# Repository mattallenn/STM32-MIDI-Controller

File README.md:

# STM32 MIDI Controller - STOMPR

For the full writeup, please check out my website:

https://mattallen.page/stompr.html

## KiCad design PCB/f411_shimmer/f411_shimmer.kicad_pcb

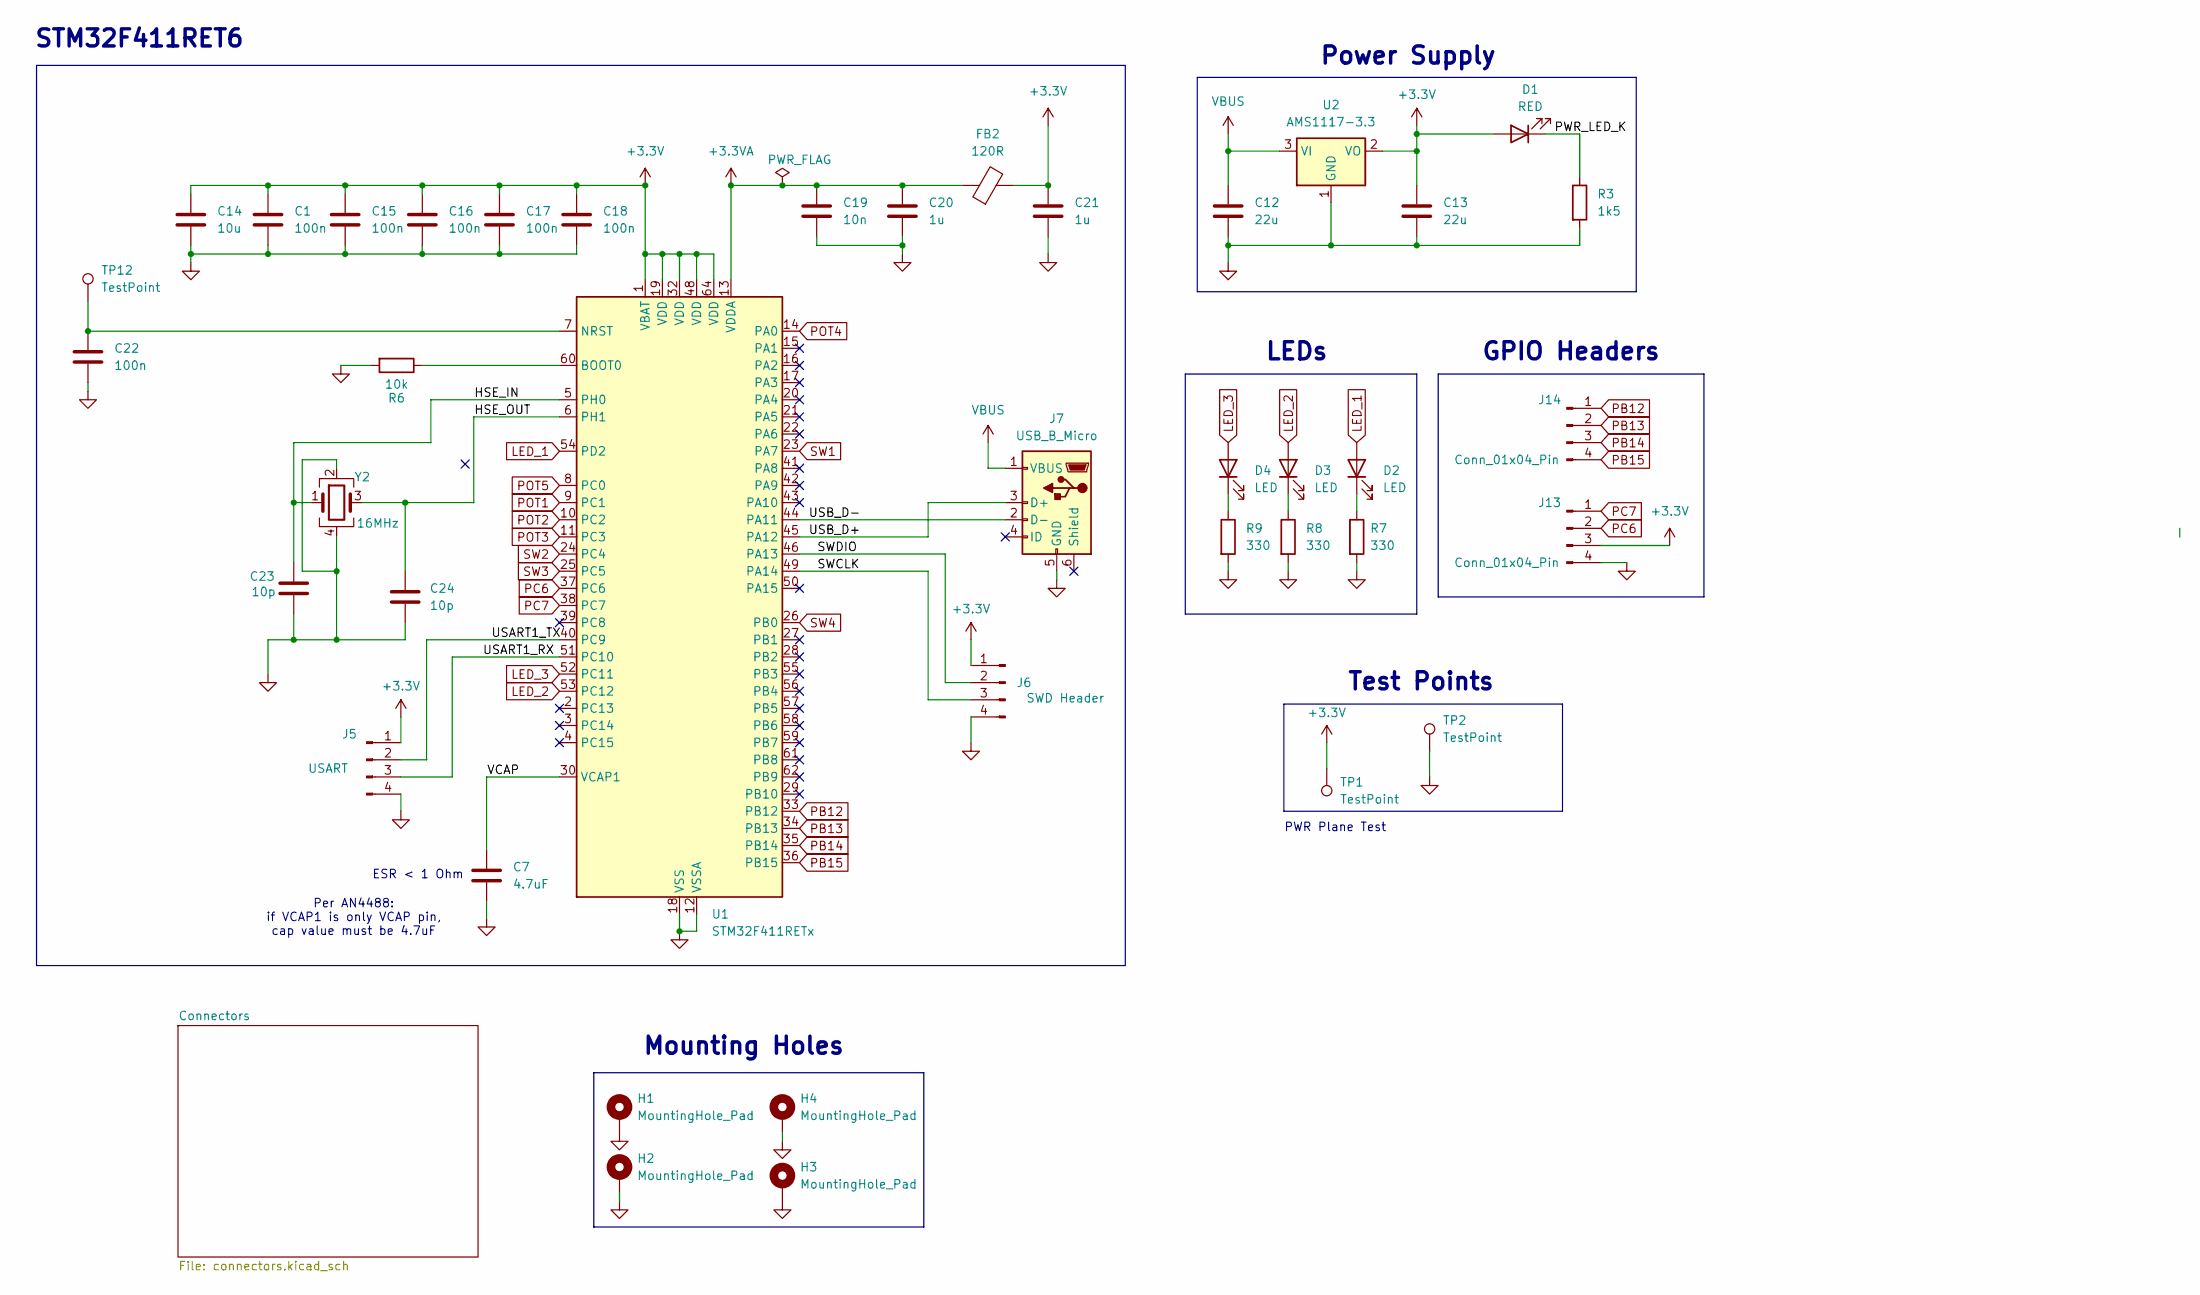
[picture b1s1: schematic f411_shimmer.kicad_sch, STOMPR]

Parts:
C1, C15, C16, C17, C18, C22: 100n; C_0603_1608Metric
C7: 4.7uF; C_0603_1608Metric
C12, C13: 22u; C_0805_2012Metric
C14: 10u; C_0603_1608Metric
C19: 10n; C_0603_1608Metric
C20, C21: 1u; C_0603_1608Metric
C23, C24: 10p; C_0603_1608Metric
D1: RED; LED_0603_1608Metric
D2, D3, D4: LED; LED_0603_1608Metric
FB2: 120R; L_0603_1608Metric
H1, H2, H3, H4: MountingHole_Pad; MountingHole_3.2mm_M3_Pad_TopBottom
J5: USART; PinHeader_1x04_P2.54mm_Vertical
J6: SWD Header; PinHeader_1x04_P2.54mm_Vertical
J7: USB_B_Micro; USB_Micro-B_Wuerth_629105150521
J13, J14: Conn_01x04_Pin; PinHeader_1x04_P2.54mm_Vertical
R3: 1k5; R_0603_1608Metric
R6: 10k; R_0603_1608Metric
R7, R8, R9: 330; R_0805_2012Metric
TP1, TP2, TP12: TestPoint; TestPoint_Pad_D1.0mm
U1: STM32F411RETx; LQFP-64_10x10mm_P0.5mm
U2: AMS1117-3.3; SOT-223-3_TabPin2
Y2: 16MHz; Crystal_SMD_3225-4Pin_3.2x2.5mm

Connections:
+3.3V: C1.1, C13.1, C14.1, C15.1, C16.1, C17.1, C18.1, C21.1, D1.2 (A), FB2.2, J5.1, J6.1, J13.3, TP1.1, U1.1 (VBAT), U1.19 (VDD), U1.32 (VDD), U1.48 (VDD), U1.64 (VDD), U2.2 (VO); also elsewhere on the board
+3.3VA: C19.1, C20.1, FB2.1, U1.13 (VDDA)
/HSE_IN: C23.1, U1.5 (PH0), Y2.1
/HSE_OUT: C24.1, U1.6 (PH1), Y2.3
/PWR_LED_K: D1.1 (K), R3.1
/SWCLK: J6.3, U1.49 (PA14)
/SWDIO: J6.2, U1.46 (PA13)
/USART1_RX: J5.3, U1.51 (PC10)
/USART1_TX: J5.2, U1.40 (PC9)
/USB_D+: J7.3 (D+), U1.45 (PA12)
/USB_D-: J7.2 (D-), U1.44 (PA11)
/VCAP: C7.1, U1.30 (VCAP1)
GND: C1.2, C7.2, C12.2, C13.2, C14.2, C15.2, C16.2, C17.2, C18.2, C19.2, C20.2, C21.2, C22.2, C23.2, C24.2, H1.1, H2.1, H3.1, H4.1, J5.4, J6.4, J7.5 (GND), J13.4, R3.2, R6.2, R7.2, R8.2, R9.2, TP2.1, U1.12 (VSSA), U1.18 (VSS), U1.31 (VSS), U1.47 (VSS), U1.63 (VSS), U2.1 (GND), Y2.2, Y2.4; also elsewhere on the board
LED_1: D2.2 (A), U1.54 (PD2)
LED_2: D3.2 (A), U1.53 (PC12)
LED_3: D4.2 (A), U1.52 (PC11)
unnamed: D2.1 (K), R7.1
unnamed: D3.1 (K), R8.1
unnamed: D4.1 (K), R9.1
unnamed: R6.1, U1.60 (BOOT0)
unnamed: C22.1, TP12.1, U1.7 (NRST)
PB12: J14.1, U1.33 (PB12)
PB13: J14.2, U1.34 (PB13)
PB14: J14.3, U1.35 (PB14)
PB15: J14.4, U1.36 (PB15)
PC6: J13.2, U1.37 (PC6)
PC7: J13.1, U1.38 (PC7)
POT1: U1.9 (PC1); also elsewhere on the board
POT2: U1.10 (PC2); also elsewhere on the board
POT3: U1.11 (PC3); also elsewhere on the board
POT4: U1.14 (PA0); also elsewhere on the board
POT5: U1.8 (PC0); also elsewhere on the board
SW1: U1.23 (PA7); also elsewhere on the board
SW2: U1.24 (PC4); also elsewhere on the board
SW3: U1.25 (PC5); also elsewhere on the board
SW4: U1.26 (PB0); also elsewhere on the board
VBUS: C12.1, J7.1 (VBUS), U2.3 (VI); also elsewhere on the board

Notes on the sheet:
LEDs
Per AN4488: if VCAP1 is only VCAP pin, cap value must be 4.7uF
Power Supply
PWR Plane Test
GPIO Headers
ESR < 1 Ohm
Mounting Holes
Test Points
STM32F411RET6

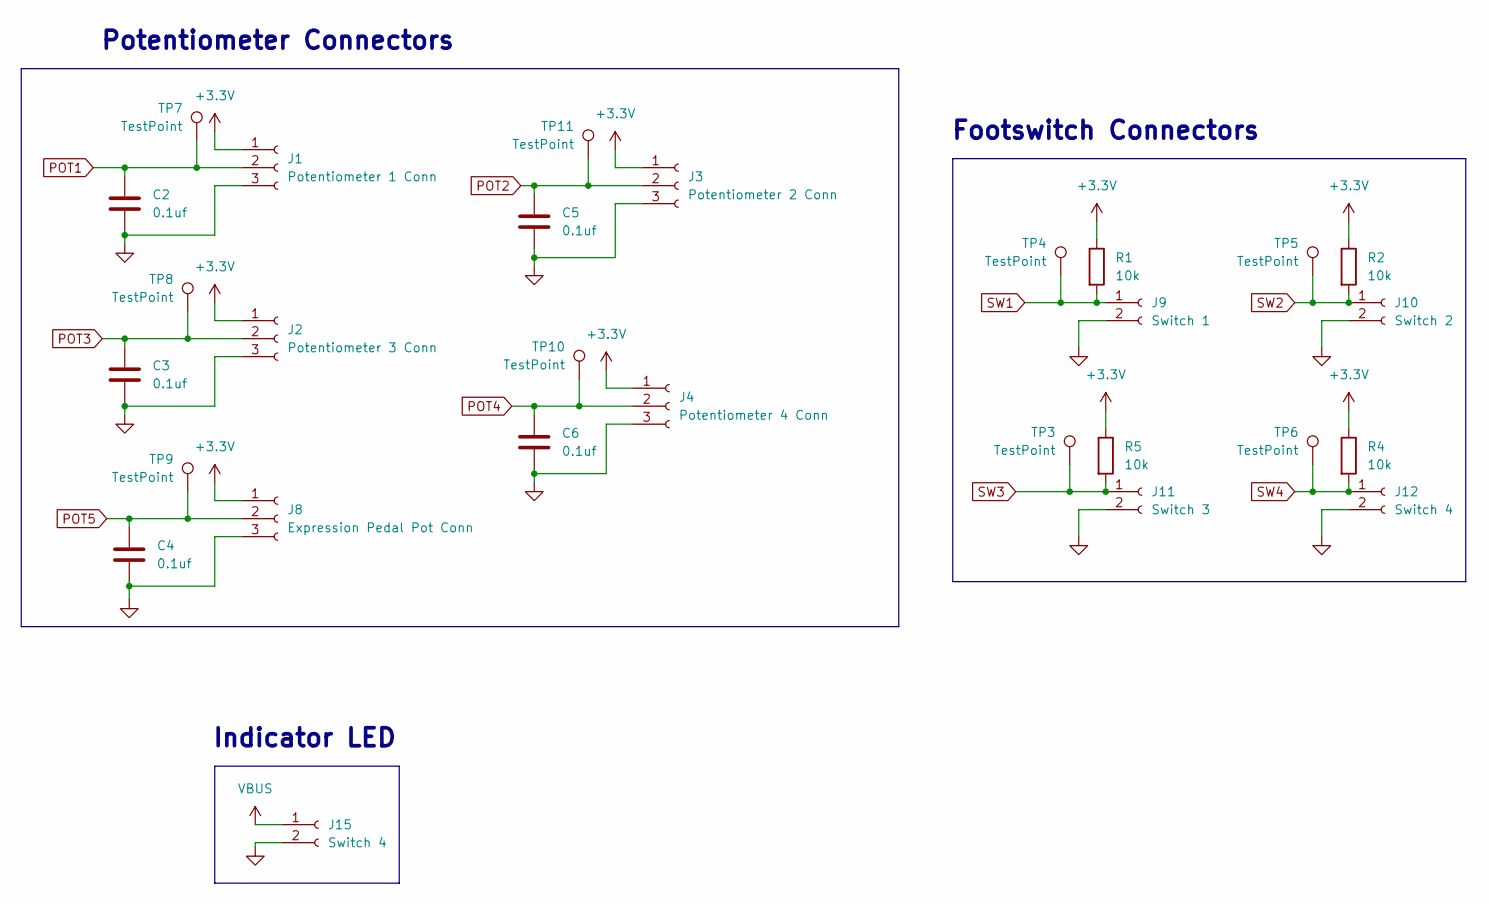
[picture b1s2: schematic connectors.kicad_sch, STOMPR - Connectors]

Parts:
C2, C3, C4, C5, C6: 0.1uf; C_0603_1608Metric
J1: Potentiometer 1 Conn; JST_EH_B3B-EH-A_1x03_P2.50mm_Vertical
J2: Potentiometer 3 Conn; JST_EH_B3B-EH-A_1x03_P2.50mm_Vertical
J3: Potentiometer 2 Conn; JST_EH_B3B-EH-A_1x03_P2.50mm_Vertical
J4: Potentiometer 4 Conn; JST_EH_B3B-EH-A_1x03_P2.50mm_Vertical
J8: Expression Pedal Pot Conn; JST_EH_B3B-EH-A_1x03_P2.50mm_Vertical
J9: Switch 1; JST_EH_B2B-EH-A_1x02_P2.50mm_Vertical
J10: Switch 2; JST_EH_B2B-EH-A_1x02_P2.50mm_Vertical
J11: Switch 3; JST_EH_B2B-EH-A_1x02_P2.50mm_Vertical
J12, J15: Switch 4; JST_EH_B2B-EH-A_1x02_P2.50mm_Vertical
R1, R2, R4, R5: 10k; R_0805_2012Metric
TP3, TP4, TP5, TP6, TP7, TP8, TP9, TP10, TP11: TestPoint; TestPoint_Pad_D1.0mm

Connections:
+3.3V: J1.1, J2.1, J3.1, J4.1, J8.1, R1.1, R2.1, R4.1, R5.1; also elsewhere on the board
GND: C2.2, C3.2, C4.2, C5.2, C6.2, J1.3, J2.3, J3.3, J4.3, J8.3, J9.2, J10.2, J11.2, J12.2, J15.2; also elsewhere on the board
POT1: C2.1, J1.2, TP7.1; also elsewhere on the board
POT2: C5.1, J3.2, TP11.1; also elsewhere on the board
POT3: C3.1, J2.2, TP8.1; also elsewhere on the board
POT4: C6.1, J4.2, TP10.1; also elsewhere on the board
POT5: C4.1, J8.2, TP9.1; also elsewhere on the board
SW1: J9.1, R1.2, TP4.1; also elsewhere on the board
SW2: J10.1, R2.2, TP5.1; also elsewhere on the board
SW3: J11.1, R5.2, TP3.1; also elsewhere on the board
SW4: J12.1, R4.2, TP6.1; also elsewhere on the board
VBUS: J15.1; also elsewhere on the board

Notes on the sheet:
Footswitch Connectors
Indicator LED
Potentiometer Connectors

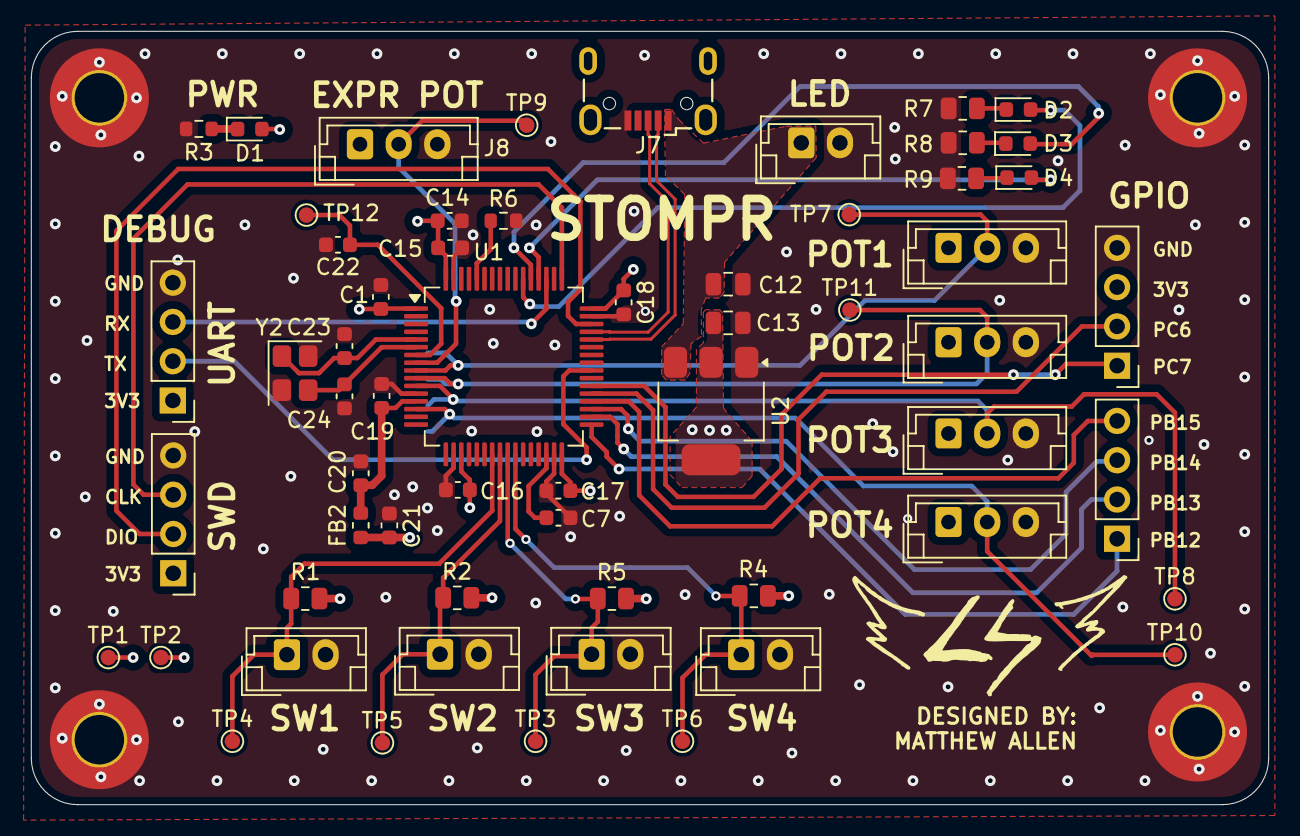
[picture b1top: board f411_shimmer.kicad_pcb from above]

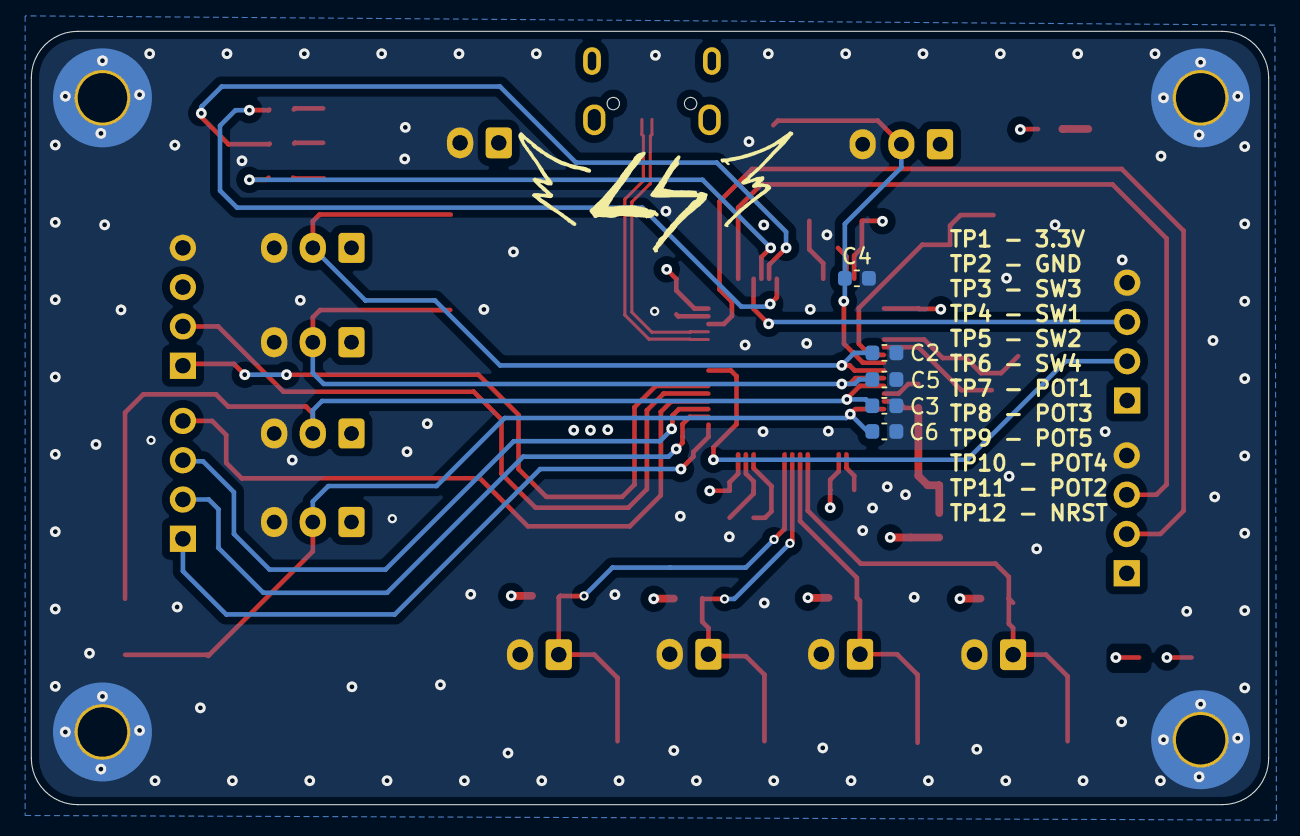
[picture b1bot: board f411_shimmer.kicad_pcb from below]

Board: 4 copper layers, 80.0 x 50.0 mm, 68 parts (5 on the bottom side), 37 nets.

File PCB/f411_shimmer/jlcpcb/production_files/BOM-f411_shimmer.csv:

Comment,Designator,Footprint,LCSC,Quantity
0.1uf,"C2,C3,C4,C5,C6",C_0603_1608Metric,C14663,5
100n,"C1,C15,C16,C17,C18,C22",C_0603_1608Metric,C14663,6
10k,"R1,R2,R4,R5",R_0805_2012Metric,C17414,4
10k,R6,R_0603_1608Metric,C25804,1
10n,C19,C_0603_1608Metric,C57112,1
10p,"C23,C24",C_0603_1608Metric,C1634,2
10u,C14,C_0603_1608Metric,C19702,1
120R,FB2,L_0603_1608Metric,C14709,1
16MHz,Y2,Crystal_SMD_3225-4Pin_3.2x2.5mm,C13738,1
1k5,R3,R_0603_1608Metric,C22843,1
1u,"C20,C21",C_0603_1608Metric,C15849,2
22u,"C12,C13",C_0805_2012Metric,C45783,2
330,"R7,R8,R9",R_0805_2012Metric,C17630,3
4.7uF,C7,C_0603_1608Metric,C19666,1
AMS1117-3.3,U2,SOT-223-3_TabPin2,C6186,1
LED,"D2,D3,D4",LED_0603_1608Metric,C2286,3
RED,D1,LED_0603_1608Metric,C2286,1
STM32F411RETx,U1,LQFP-64_10x10mm_P0.5mm,C94355,1
Switch 4,J12,JST_EH_B2B-EH-A_1x02_P2.50mm_Vertical,,1
TestPoint,TP4,TestPoint_Pad_D1.0mm,,1
Switch 3,J11,JST_EH_B2B-EH-A_1x02_P2.50mm_Vertical,,1
TestPoint,TP7,TestPoint_Pad_D1.0mm,,1
TestPoint,TP10,TestPoint_Pad_D1.0mm,,1
USART,J5,PinHeader_1x04_P2.54mm_Vertical,,1
Potentiometer 1 Conn,J1,JST_EH_B3B-EH-A_1x03_P2.50mm_Vertical,,1
Switch 4,J15,JST_EH_B2B-EH-A_1x02_P2.50mm_Vertical,,1
Expression Pedal Pot Conn,J8,JST_EH_B3B-EH-A_1x03_P2.50mm_Vertical,,1
Conn_01x04_Pin,J13,PinHeader_1x04_P2.54mm_Vertical,,1
SWD Header,J6,PinHeader_1x04_P2.54mm_Vertical,,1
Switch 2,J10,JST_EH_B2B-EH-A_1x02_P2.50mm_Vertical,,1
TestPoint,TP6,TestPoint_Pad_D1.0mm,,1
Switch 1,J9,JST_EH_B2B-EH-A_1x02_P2.50mm_Vertical,,1
Potentiometer 2 Conn,J3,JST_EH_B3B-EH-A_1x03_P2.50mm_Vertical,,1
TestPoint,TP3,TestPoint_Pad_D1.0mm,,1
TestPoint,TP8,TestPoint_Pad_D1.0mm,,1
USB_B_Micro,J7,USB_Micro-B_Wuerth_629105150521,,1
TestPoint,TP2,TestPoint_Pad_D1.0mm,,1
TestPoint,TP9,TestPoint_Pad_D1.0mm,,1
Potentiometer 4 Conn,J4,JST_EH_B3B-EH-A_1x03_P2.50mm_Vertical,,1
TestPoint,TP1,TestPoint_Pad_D1.0mm,,1
TestPoint,TP5,TestPoint_Pad_D1.0mm,,1
Potentiometer 3 Conn,J2,JST_EH_B3B-EH-A_1x03_P2.50mm_Vertical,,1
Conn_01x04_Pin,J14,PinHeader_1x04_P2.54mm_Vertical,,1
TestPoint,TP12,TestPoint_Pad_D1.0mm,,1
TestPoint,TP11,TestPoint_Pad_D1.0mm,,1

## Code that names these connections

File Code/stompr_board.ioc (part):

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Mcu.Name=STM32F411R(C-E)Tx
Mcu.Package=LQFP64
Mcu.UserName=STM32F411RETx
PA0-WKUP.Signal=ADCx_IN0
PA11.Mode=Device_Only
PA11.Signal=USB_OTG_FS_DM
PA12.Mode=Device_Only
PA12.Signal=USB_OTG_FS_DP
PA13.Mode=Serial_Wire
PA13.Signal=SYS_JTMS-SWDIO
PA14.Mode=Serial_Wire
PA14.Signal=SYS_JTCK-SWCLK
PA7.Signal=GPIO_Input
PA8.Mode=Clock-out-1
PA8.Signal=RCC_MCO_1
PB0.Signal=GPIO_Input
PC1.Signal=ADCx_IN11
PC11.Signal=GPIO_Output
PC12.Signal=GPIO_Output
PC2.Signal=ADCx_IN12
PC3.Signal=ADCx_IN13
PC4.Signal=GPIO_Input
PC5.Signal=GPIO_Input
PC9.Mode=Clock-out-2
PC9.Signal=RCC_MCO_2
PD2.Signal=GPIO_Output
PH0\ -\ OSC_IN.Mode=HSE-External-Oscillator
PH0\ -\ OSC_IN.Signal=RCC_OSC_IN
PH1\ -\ OSC_OUT.Mode=HSE-External-Oscillator
PH1\ -\ OSC_OUT.Signal=RCC_OSC_OUT
RCC.HSE_VALUE=16000000
RCC.SYSCLKFreq_VALUE=96000000
RCC.SYSCLKSource=RCC_SYSCLKSOURCE_PLLCLK
board=custom

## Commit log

2026-03-13 uploaded files
2026-03-19 uploaded render image
2026-03-21 organized + updated README
2026-03-21 organized repo
2026-03-21 fixed image paths
2026-04-11 project complete! updated code
2026-04-11 added PCB files
